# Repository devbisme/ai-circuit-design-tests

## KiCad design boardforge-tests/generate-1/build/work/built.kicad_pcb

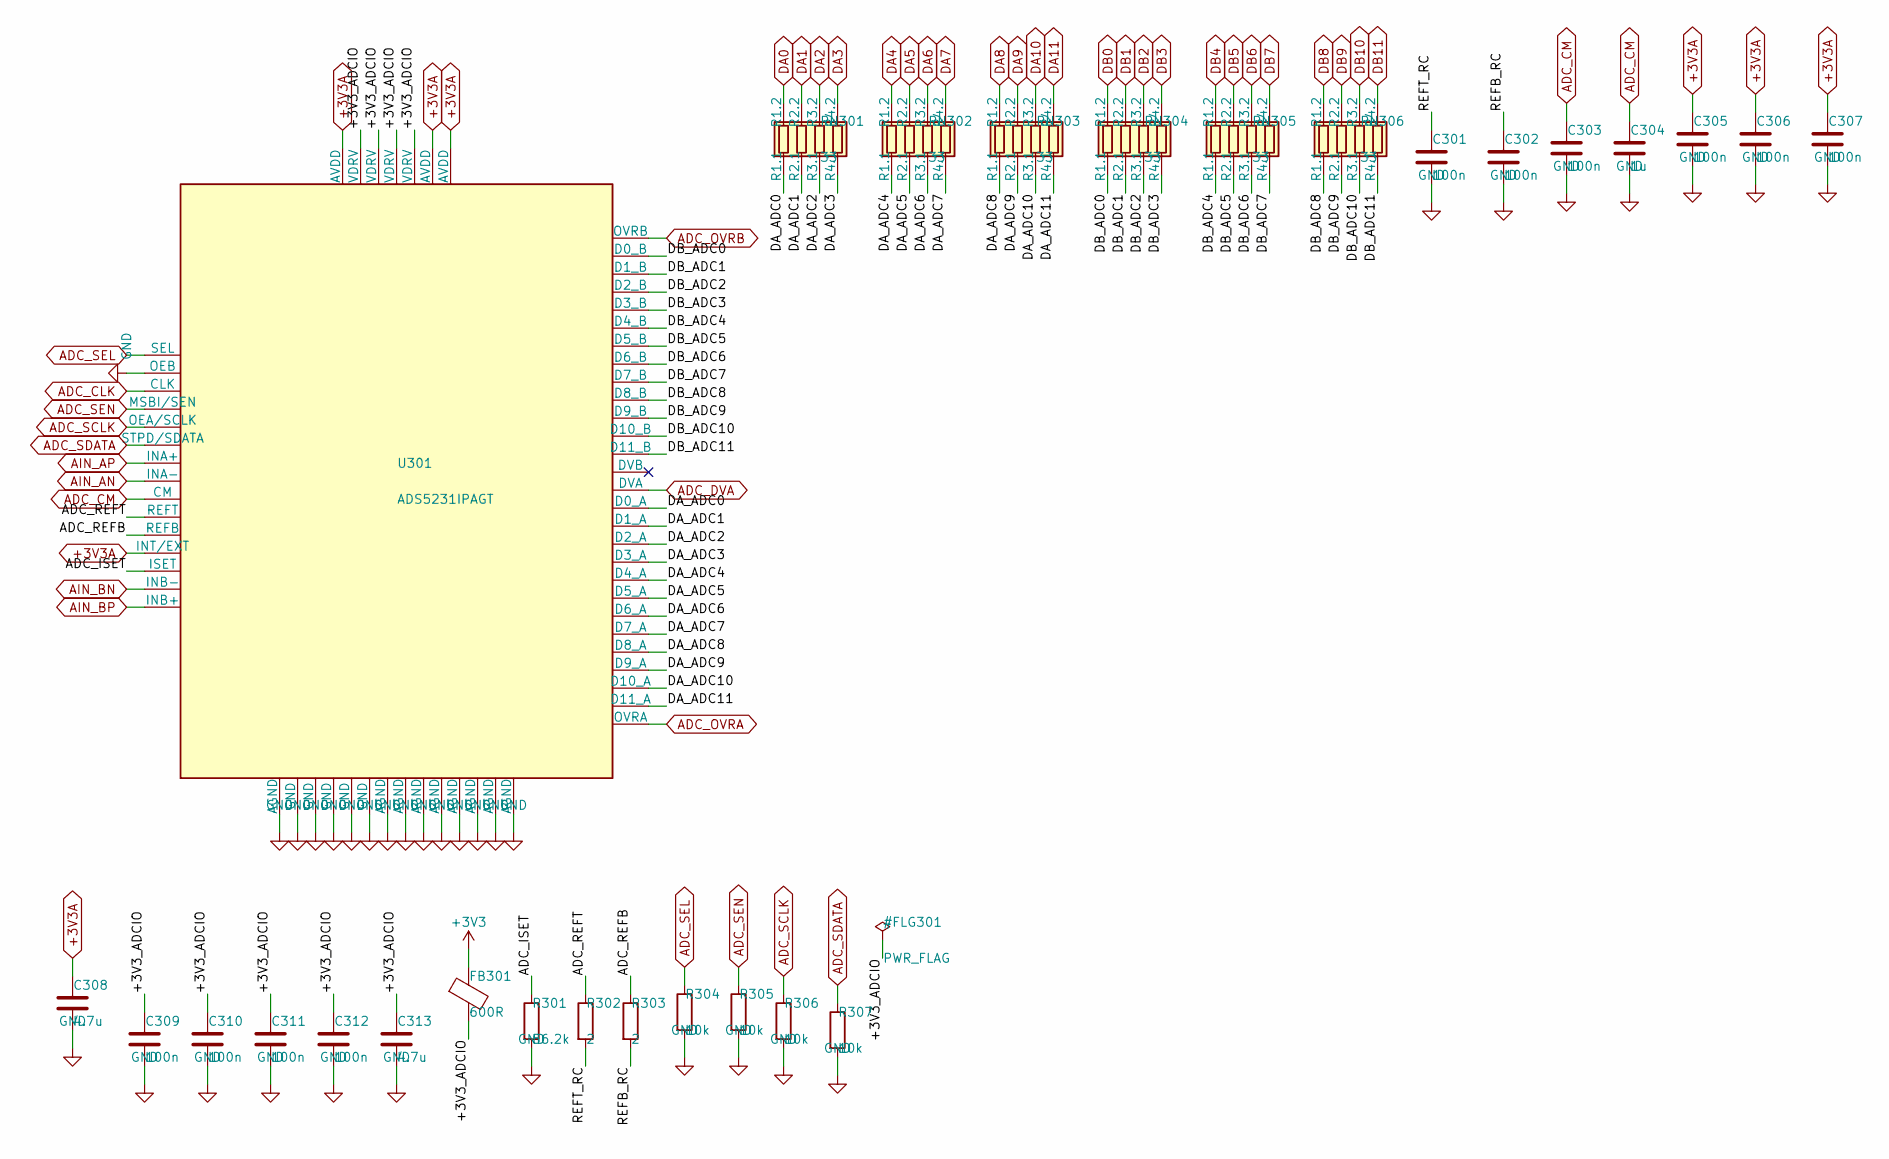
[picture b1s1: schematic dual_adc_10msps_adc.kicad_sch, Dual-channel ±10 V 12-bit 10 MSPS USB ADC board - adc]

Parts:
C301, C302, C303, C305, C306, C307, C309, C310, C311, C312: 100n; C_0402_1005Metric; MPN CL05B104KB54PNC; LCSC C307331
C304: 1u; C_0402_1005Metric; MPN CL05A105KA5NQNC; LCSC C52923
C308, C313: 4.7u; C_0603_1608Metric; MPN CL10A475KO8NNNC; LCSC C19666
FB301: 600R; L_0603_1608Metric; MPN BLM18KG601SN1D; LCSC C85833
R301: 56.2k; R_0402_1005Metric; MPN FRC0402F5622TS; LCSC C5126096
R302, R303: 2; R_0402_1005Metric; MPN FRC0402F2R00TS; LCSC C2998051
R304, R305, R306, R307: 10k; R_0402_1005Metric; MPN 0402WGF1002TCE; LCSC C25744
RN301, RN302, RN303, RN304, RN305, RN306: 33; R_Array_Convex_4x0402; MPN 4D02WGJ0330TCE; LCSC C25501
U301: ADS5231IPAGT; TQFP-64_10x10mm_P0.5mm; MPN ADS5231IPAGT; LCSC C2670079

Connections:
+3V3: FB301.1; also elsewhere on the board
+3V3A: C305.1, C306.1, C307.1, C308.1, U301.3 (AVDD), U301.46 (AVDD), U301.56 (INT/EXT), U301.57 (AVDD); also elsewhere on the board
/adc/+3V3_ADCIO: C309.1, C310.1, C311.1, C312.1, C313.1, FB301.2, U301.5 (VDRV), U301.8 (VDRV), U301.40 (VDRV), U301.43 (VDRV)
/adc/ADC_ISET: R301.1, U301.60 (ISET)
/adc/ADC_REFB: R303.1, U301.54 (REFB)
/adc/ADC_REFT: R302.1, U301.53 (REFT)
/adc/DA_ADC0: RN301.1 (R1.1), U301.27 (D0_A)
/adc/DA_ADC1: RN301.2 (R2.1), U301.28 (D1_A)
/adc/DA_ADC2: RN301.3 (R3.1), U301.29 (D2_A)
/adc/DA_ADC3: RN301.4 (R4.1), U301.30 (D3_A)
/adc/DA_ADC4: RN302.1 (R1.1), U301.31 (D4_A)
/adc/DA_ADC5: RN302.2 (R2.1), U301.32 (D5_A)
/adc/DA_ADC6: RN302.3 (R3.1), U301.33 (D6_A)
/adc/DA_ADC7: RN302.4 (R4.1), U301.34 (D7_A)
/adc/DA_ADC8: RN303.1 (R1.1), U301.35 (D8_A)
/adc/DA_ADC9: RN303.2 (R2.1), U301.36 (D9_A)
/adc/DA_ADC10: RN303.3 (R3.1), U301.37 (D10_A)
/adc/DA_ADC11: RN303.4 (R4.1), U301.38 (D11_A)
/adc/DB_ADC0: RN304.1 (R1.1), U301.10 (D0_B)
/adc/DB_ADC1: RN304.2 (R2.1), U301.11 (D1_B)
/adc/DB_ADC2: RN304.3 (R3.1), U301.12 (D2_B)
/adc/DB_ADC3: RN304.4 (R4.1), U301.13 (D3_B)
/adc/DB_ADC4: RN305.1 (R1.1), U301.14 (D4_B)
/adc/DB_ADC5: RN305.2 (R2.1), U301.15 (D5_B)
/adc/DB_ADC6: RN305.3 (R3.1), U301.16 (D6_B)
/adc/DB_ADC7: RN305.4 (R4.1), U301.17 (D7_B)
/adc/DB_ADC8: RN306.1 (R1.1), U301.18 (D8_B)
/adc/DB_ADC9: RN306.2 (R2.1), U301.19 (D9_B)
/adc/DB_ADC10: RN306.3 (R3.1), U301.20 (D10_B)
/adc/DB_ADC11: RN306.4 (R4.1), U301.21 (D11_B)
/adc/REFB_RC: C302.1, R303.2
/adc/REFT_RC: C301.1, R302.2
ADC_CLK: U301.24 (CLK); also elsewhere on the board
ADC_CM: C303.1, C304.1, U301.52 (CM); also elsewhere on the board
ADC_DVA: U301.26 (DVA); also elsewhere on the board
ADC_OVRA: U301.39 (OVRA); also elsewhere on the board
ADC_OVRB: U301.9 (OVRB); also elsewhere on the board
ADC_SCLK: R306.1, U301.42 (OEA/SCLK); also elsewhere on the board
ADC_SDATA: R307.1, U301.45 (STPD/SDATA); also elsewhere on the board
ADC_SEL: R304.1, U301.1 (SEL); also elsewhere on the board
ADC_SEN: R305.1, U301.41 (MSBI/SEN); also elsewhere on the board
AIN_AN: U301.51 (INA-); also elsewhere on the board
AIN_AP: U301.50 (INA+); also elsewhere on the board
AIN_BN: U301.62 (INB-); also elsewhere on the board
AIN_BP: U301.63 (INB+); also elsewhere on the board
DA0: RN301.8 (R1.2); also elsewhere on the board
DA1: RN301.7 (R2.2); also elsewhere on the board
DA2: RN301.6 (R3.2); also elsewhere on the board
DA3: RN301.5 (R4.2); also elsewhere on the board
DA4: RN302.8 (R1.2); also elsewhere on the board
DA5: RN302.7 (R2.2); also elsewhere on the board
DA6: RN302.6 (R3.2); also elsewhere on the board
DA7: RN302.5 (R4.2); also elsewhere on the board
DA8: RN303.8 (R1.2); also elsewhere on the board
DA9: RN303.7 (R2.2); also elsewhere on the board
DA10: RN303.6 (R3.2); also elsewhere on the board
DA11: RN303.5 (R4.2); also elsewhere on the board
DB0: RN304.8 (R1.2); also elsewhere on the board
DB1: RN304.7 (R2.2); also elsewhere on the board
DB2: RN304.6 (R3.2); also elsewhere on the board
DB3: RN304.5 (R4.2); also elsewhere on the board
DB4: RN305.8 (R1.2); also elsewhere on the board
DB5: RN305.7 (R2.2); also elsewhere on the board
DB6: RN305.6 (R3.2); also elsewhere on the board
DB7: RN305.5 (R4.2); also elsewhere on the board
DB8: RN306.8 (R1.2); also elsewhere on the board
DB9: RN306.7 (R2.2); also elsewhere on the board
DB10: RN306.6 (R3.2); also elsewhere on the board
DB11: RN306.5 (R4.2); also elsewhere on the board
GND: C301.2, C302.2, C303.2, C304.2, C305.2, C306.2, C307.2, C308.2, C309.2, C310.2, C311.2, C312.2, C313.2, R301.2, R304.2, R305.2, R306.2, R307.2, U301.2 (AGND), U301.4 (GND), U301.6 (OEB), U301.7 (GND), U301.23 (GND), U301.25 (GND), U301.44 (GND), U301.47 (AGND), U301.48 (AGND), U301.49 (AGND), U301.55 (AGND), U301.58 (AGND), U301.59 (AGND), U301.61 (AGND), U301.64 (AGND); also elsewhere on the board

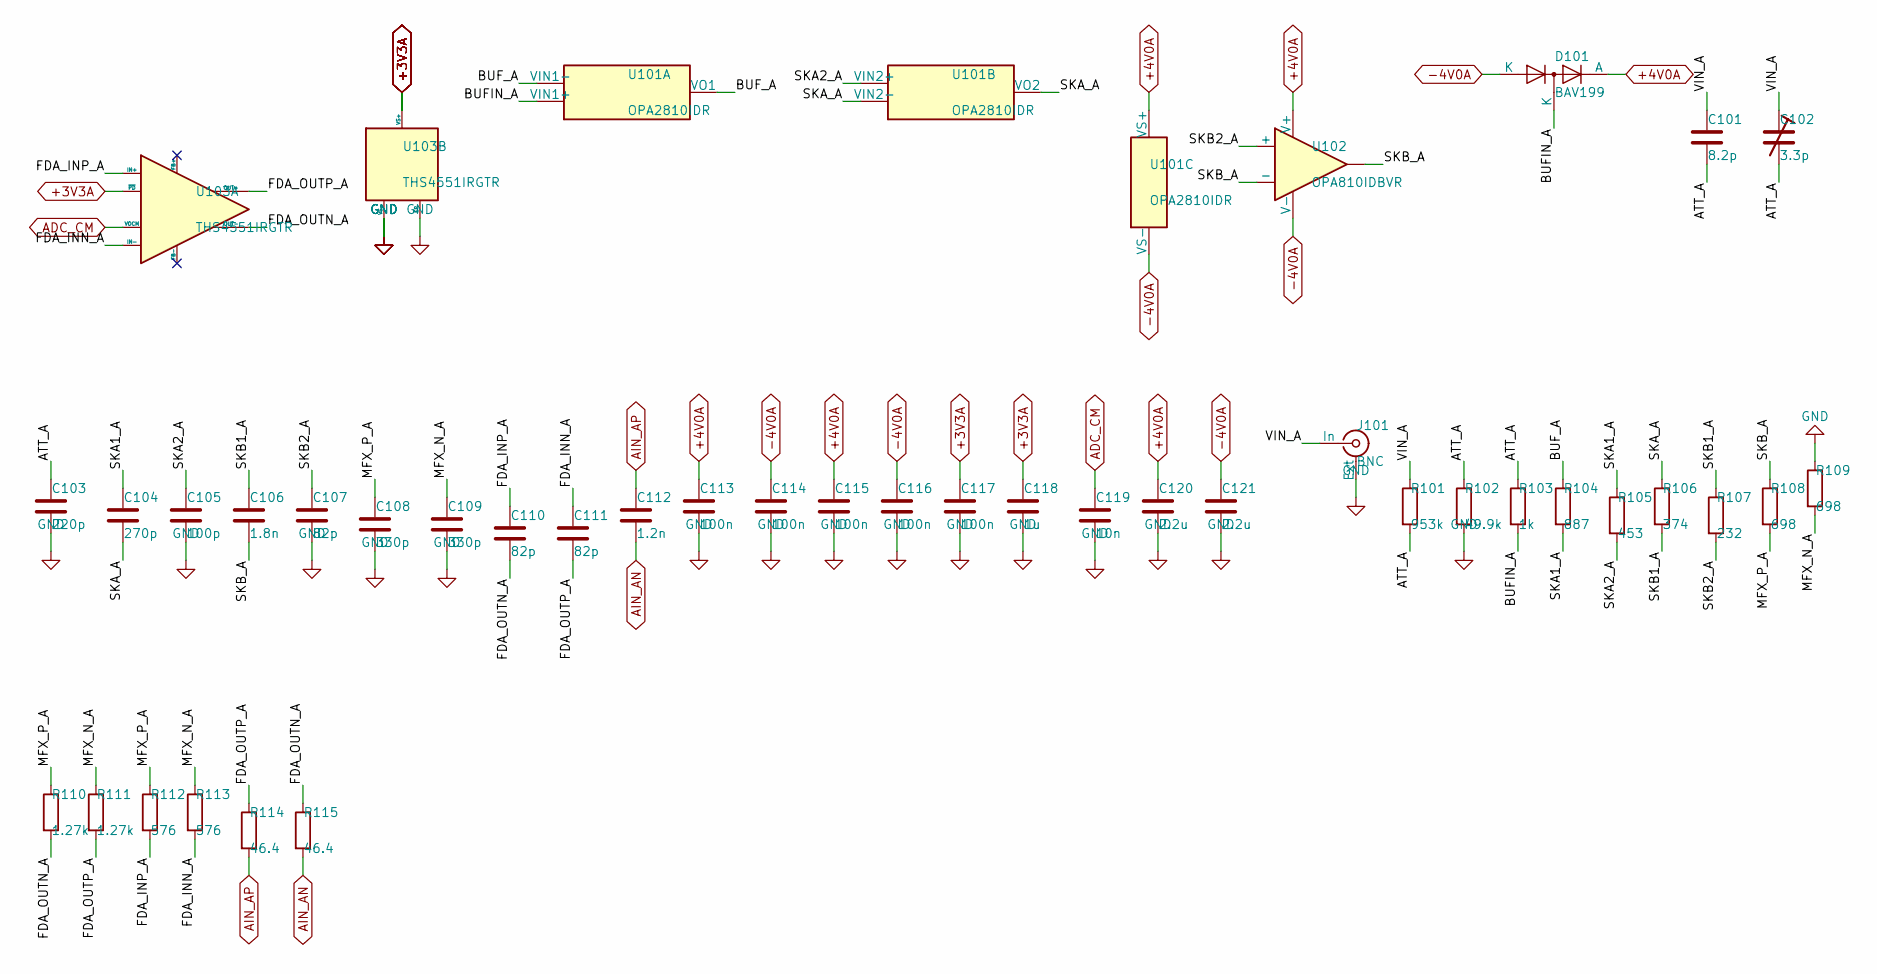
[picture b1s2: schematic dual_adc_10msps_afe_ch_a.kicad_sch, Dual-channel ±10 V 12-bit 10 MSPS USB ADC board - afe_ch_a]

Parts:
C101: 8.2p; C_0603_1608Metric; MPN GQM1875C2E8R2CB12D; LCSC C3874850
C102: 3.3p; C_Trimmer_SEHWA_STC3MA06; MPN STC3MA06-T1; LCSC C22468120
C103: 220p; C_0603_1608Metric; MPN GCM1885C2A221JA16D; LCSC C388907
C104: 270p; C_0402_1005Metric; MPN GRM1555C1H271GA01D; LCSC C161546
C105: 100p; C_0603_1608Metric; MPN 0603CG101G500NT; LCSC C182932
C106: 1.8n; C_0603_1608Metric; MPN GRM1885C1H182FA01D; LCSC C882525
C107, C110, C111: 82p; C_0603_1608Metric; MPN GQM1875C2E820GB12D; LCSC C2171259
C108, C109: 330p; C_0402_1005Metric; MPN GRM1555C1H331GA01D; LCSC C237507
C112: 1.2n; C_0603_1608Metric; MPN GCM1885C1H122FA16D; LCSC C1517816
C113, C114, C115, C116, C117: 100n; C_0402_1005Metric; MPN CL05B104KB54PNC; LCSC C307331
C118: 1u; C_0402_1005Metric; MPN CL05A105KA5NQNC; LCSC C52923
C119: 10n; C_0402_1005Metric; MPN CL05B103KB5NNNC; LCSC C15195
C120, C121: 2.2u; C_0603_1608Metric; MPN CL10A225KO8NNNC; LCSC C23630
D101: BAV199; SOT-23; MPN BAV199; LCSC C68971
J101: BNC; BNC_KH-BNC50-3511; MPN KH-BNC50-3511; LCSC C2837587
R101: 953k; R_1206_3216Metric; MPN WR12X9533FTL; LCSC C368327
R102: 49.9k; R_0603_1608Metric; MPN 0603WAF4992T5E; LCSC C23184
R103: 1k; R_0603_1608Metric; MPN 0603WAF1001T5E; LCSC C21190
R104: 887; R_0402_1005Metric; MPN CRCW0402887RFKED; LCSC C4012675
R105: 453; R_0402_1005Metric; MPN FRC0402F4530TS; LCSC C5126227
R106: 374; R_0402_1005Metric; MPN RMS04FT3740; LCSC C208875
R107: 232; R_0402_1005Metric; MPN GR0402F232RTAG00; LCSC C49655645
R108, R109: 698; R_0402_1005Metric; MPN GR0402F698RTAG00; LCSC C49655034
R110, R111: 1.27k; R_0402_1005Metric; MPN FRC0402F1271TS; LCSC C3013151
R112, R113: 576; R_0402_1005Metric; MPN 0402WGF5760TCE; LCSC C45320
R114, R115: 46.4; R_0402_1005Metric; MPN RC0402FR-0746R4L; LCSC C273734
U101: OPA2810IDR; SOIC-8_3.9x4.9mm_P1.27mm; MPN OPA2810IDR; LCSC C1849413
U102: OPA810IDBVR; SOT-23-5; MPN OPA810IDBVR; LCSC C2833513
U103: THS4551IRGTR; VQFN-16-1EP_3x3mm_P0.5mm_EP1.68x1.68mm; MPN THS4551IRGTR; LCSC C2869590

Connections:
+3V3A: C117.1, C118.1, U103.5 (VS+), U103.6 (VS+), U103.7 (VS+), U103.8 (VS+), U103.12 (~PD); also elsewhere on the board
+4V0A: C113.1, C115.1, C120.1, D101.2 (A), U101.8 (VS+), U102.5 (V+); also elsewhere on the board
-4V0A: C114.1, C116.1, C121.1, D101.1 (K), U101.4 (VS-), U102.2 (V-); also elsewhere on the board
/afe_ch_a/ATT_A: C101.2, C102.2, C103.1, R101.2, R102.1, R103.1
/afe_ch_a/BUFIN_A: D101.3 (K), R103.2, U101.3 (VIN1+)
/afe_ch_a/BUF_A: R104.1, U101.1 (VO1), U101.2 (VIN1-)
/afe_ch_a/FDA_INN_A: C111.1, R113.2, U103.3 (IN-)
/afe_ch_a/FDA_INP_A: C110.1, R112.2, U103.2 (IN+)
/afe_ch_a/FDA_OUTN_A: C110.2, R110.2, R115.1, U103.11 (OUT-)
/afe_ch_a/FDA_OUTP_A: C111.2, R111.2, R114.1, U103.10 (OUT+)
/afe_ch_a/MFX_N_A: C109.1, R109.2, R111.1, R113.1
/afe_ch_a/MFX_P_A: C108.1, R108.2, R110.1, R112.1
/afe_ch_a/SKA1_A: C104.1, R104.2, R105.1
/afe_ch_a/SKA2_A: C105.1, R105.2, U101.5 (VIN2+)
/afe_ch_a/SKA_A: C104.2, R106.1, U101.6 (VIN2-), U101.7 (VO2)
/afe_ch_a/SKB1_A: C106.1, R106.2, R107.1
/afe_ch_a/SKB2_A: C107.1, R107.2, U102.3 (+)
/afe_ch_a/SKB_A: C106.2, R108.1, U102.1, U102.4 (-)
/afe_ch_a/VIN_A: C101.1, C102.1, J101.1 (In), R101.1
ADC_CM: C119.1, U103.9 (VOCM); also elsewhere on the board
AIN_AN: C112.2, R115.2; also elsewhere on the board
AIN_AP: C112.1, R114.2; also elsewhere on the board
GND: C103.2, C105.2, C107.2, C108.2, C109.2, C113.2, C114.2, C115.2, C116.2, C117.2, C118.2, C119.2, C120.2, C121.2, J101.2 (Ext), R102.2, R109.1, U103.13 (VS-), U103.14 (VS-), U103.15 (VS-), U103.16 (VS-), U103.17 (EP); also elsewhere on the board

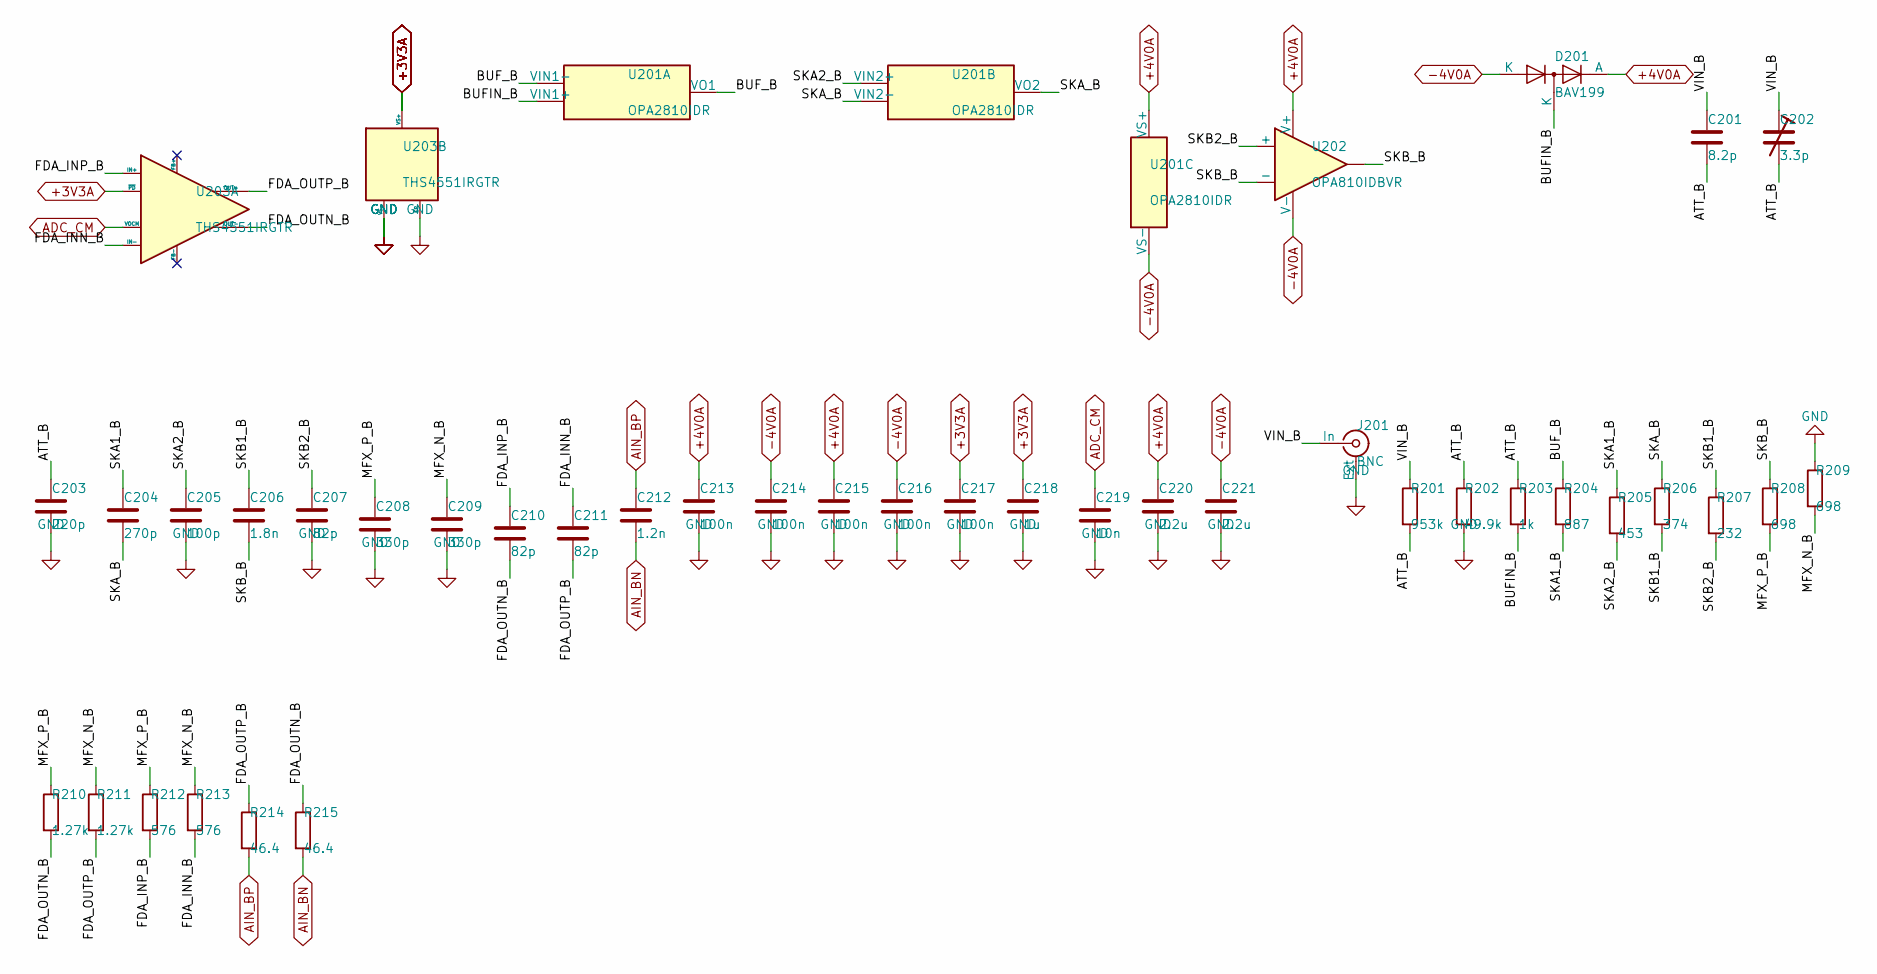
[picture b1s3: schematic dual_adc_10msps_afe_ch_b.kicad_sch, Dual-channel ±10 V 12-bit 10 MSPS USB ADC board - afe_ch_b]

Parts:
C201: 8.2p; C_0603_1608Metric; MPN GQM1875C2E8R2CB12D; LCSC C3874850
C202: 3.3p; C_Trimmer_SEHWA_STC3MA06; MPN STC3MA06-T1; LCSC C22468120
C203: 220p; C_0603_1608Metric; MPN GCM1885C2A221JA16D; LCSC C388907
C204: 270p; C_0402_1005Metric; MPN GRM1555C1H271GA01D; LCSC C161546
C205: 100p; C_0603_1608Metric; MPN 0603CG101G500NT; LCSC C182932
C206: 1.8n; C_0603_1608Metric; MPN GRM1885C1H182FA01D; LCSC C882525
C207, C210, C211: 82p; C_0603_1608Metric; MPN GQM1875C2E820GB12D; LCSC C2171259
C208, C209: 330p; C_0402_1005Metric; MPN GRM1555C1H331GA01D; LCSC C237507
C212: 1.2n; C_0603_1608Metric; MPN GCM1885C1H122FA16D; LCSC C1517816
C213, C214, C215, C216, C217: 100n; C_0402_1005Metric; MPN CL05B104KB54PNC; LCSC C307331
C218: 1u; C_0402_1005Metric; MPN CL05A105KA5NQNC; LCSC C52923
C219: 10n; C_0402_1005Metric; MPN CL05B103KB5NNNC; LCSC C15195
C220, C221: 2.2u; C_0603_1608Metric; MPN CL10A225KO8NNNC; LCSC C23630
D201: BAV199; SOT-23; MPN BAV199; LCSC C68971
J201: BNC; BNC_KH-BNC50-3511; MPN KH-BNC50-3511; LCSC C2837587
R201: 953k; R_1206_3216Metric; MPN WR12X9533FTL; LCSC C368327
R202: 49.9k; R_0603_1608Metric; MPN 0603WAF4992T5E; LCSC C23184
R203: 1k; R_0603_1608Metric; MPN 0603WAF1001T5E; LCSC C21190
R204: 887; R_0402_1005Metric; MPN CRCW0402887RFKED; LCSC C4012675
R205: 453; R_0402_1005Metric; MPN FRC0402F4530TS; LCSC C5126227
R206: 374; R_0402_1005Metric; MPN RMS04FT3740; LCSC C208875
R207: 232; R_0402_1005Metric; MPN GR0402F232RTAG00; LCSC C49655645
R208, R209: 698; R_0402_1005Metric; MPN GR0402F698RTAG00; LCSC C49655034
R210, R211: 1.27k; R_0402_1005Metric; MPN FRC0402F1271TS; LCSC C3013151
R212, R213: 576; R_0402_1005Metric; MPN 0402WGF5760TCE; LCSC C45320
R214, R215: 46.4; R_0402_1005Metric; MPN RC0402FR-0746R4L; LCSC C273734
U201: OPA2810IDR; SOIC-8_3.9x4.9mm_P1.27mm; MPN OPA2810IDR; LCSC C1849413
U202: OPA810IDBVR; SOT-23-5; MPN OPA810IDBVR; LCSC C2833513
U203: THS4551IRGTR; VQFN-16-1EP_3x3mm_P0.5mm_EP1.68x1.68mm; MPN THS4551IRGTR; LCSC C2869590

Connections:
+3V3A: C217.1, C218.1, U203.5 (VS+), U203.6 (VS+), U203.7 (VS+), U203.8 (VS+), U203.12 (~PD); also elsewhere on the board
+4V0A: C213.1, C215.1, C220.1, D201.2 (A), U201.8 (VS+), U202.5 (V+); also elsewhere on the board
-4V0A: C214.1, C216.1, C221.1, D201.1 (K), U201.4 (VS-), U202.2 (V-); also elsewhere on the board
/afe_ch_b/ATT_B: C201.2, C202.2, C203.1, R201.2, R202.1, R203.1
/afe_ch_b/BUFIN_B: D201.3 (K), R203.2, U201.3 (VIN1+)
/afe_ch_b/BUF_B: R204.1, U201.1 (VO1), U201.2 (VIN1-)
/afe_ch_b/FDA_INN_B: C211.1, R213.2, U203.3 (IN-)
/afe_ch_b/FDA_INP_B: C210.1, R212.2, U203.2 (IN+)
/afe_ch_b/FDA_OUTN_B: C210.2, R210.2, R215.1, U203.11 (OUT-)
/afe_ch_b/FDA_OUTP_B: C211.2, R211.2, R214.1, U203.10 (OUT+)
/afe_ch_b/MFX_N_B: C209.1, R209.2, R211.1, R213.1
/afe_ch_b/MFX_P_B: C208.1, R208.2, R210.1, R212.1
/afe_ch_b/SKA1_B: C204.1, R204.2, R205.1
/afe_ch_b/SKA2_B: C205.1, R205.2, U201.5 (VIN2+)
/afe_ch_b/SKA_B: C204.2, R206.1, U201.6 (VIN2-), U201.7 (VO2)
/afe_ch_b/SKB1_B: C206.1, R206.2, R207.1
/afe_ch_b/SKB2_B: C207.1, R207.2, U202.3 (+)
/afe_ch_b/SKB_B: C206.2, R208.1, U202.1, U202.4 (-)
/afe_ch_b/VIN_B: C201.1, C202.1, J201.1 (In), R201.1
ADC_CM: C219.1, U203.9 (VOCM); also elsewhere on the board
AIN_BN: C212.2, R215.2; also elsewhere on the board
AIN_BP: C212.1, R214.2; also elsewhere on the board
GND: C203.2, C205.2, C207.2, C208.2, C209.2, C213.2, C214.2, C215.2, C216.2, C217.2, C218.2, C219.2, C220.2, C221.2, J201.2 (Ext), R202.2, R209.1, U203.13 (VS-), U203.14 (VS-), U203.15 (VS-), U203.16 (VS-), U203.17 (EP); also elsewhere on the board

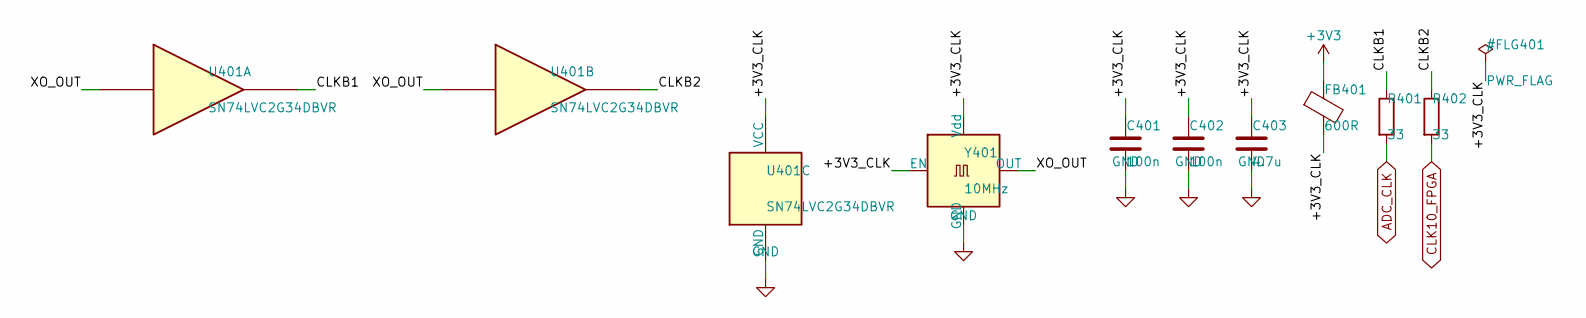
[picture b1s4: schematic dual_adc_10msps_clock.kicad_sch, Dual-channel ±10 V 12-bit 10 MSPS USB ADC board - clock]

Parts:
C401, C402: 100n; C_0402_1005Metric; MPN CL05B104KB54PNC; LCSC C307331
C403: 4.7u; C_0603_1608Metric; MPN CL10A475KO8NNNC; LCSC C19666
FB401: 600R; L_0603_1608Metric; MPN BLM18KG601SN1D; LCSC C85833
R401, R402: 33; R_0402_1005Metric; MPN 0402WGF330JTCE; LCSC C25105
U401: SN74LVC2G34DBVR; SOT-23-6; MPN SN74LVC2G34DBVR; LCSC C7394039
Y401: 10MHz; Oscillator_SMD_Abracon_ASE-4Pin_3.2x2.5mm; MPN SX3M10.000B10F20TNN; LCSC C5452682

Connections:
+3V3: FB401.1; also elsewhere on the board
/clock/+3V3_CLK: C401.1, C402.1, C403.1, FB401.2, U401.5 (VCC), Y401.1 (EN), Y401.4 (Vdd)
/clock/CLKB1: R401.1, U401.6
/clock/CLKB2: R402.1, U401.4
/clock/XO_OUT: U401.1, U401.3, Y401.3 (OUT)
ADC_CLK: R401.2; also elsewhere on the board
CLK10_FPGA: R402.2; also elsewhere on the board
GND: C401.2, C402.2, C403.2, U401.2 (GND), Y401.2 (GND); also elsewhere on the board

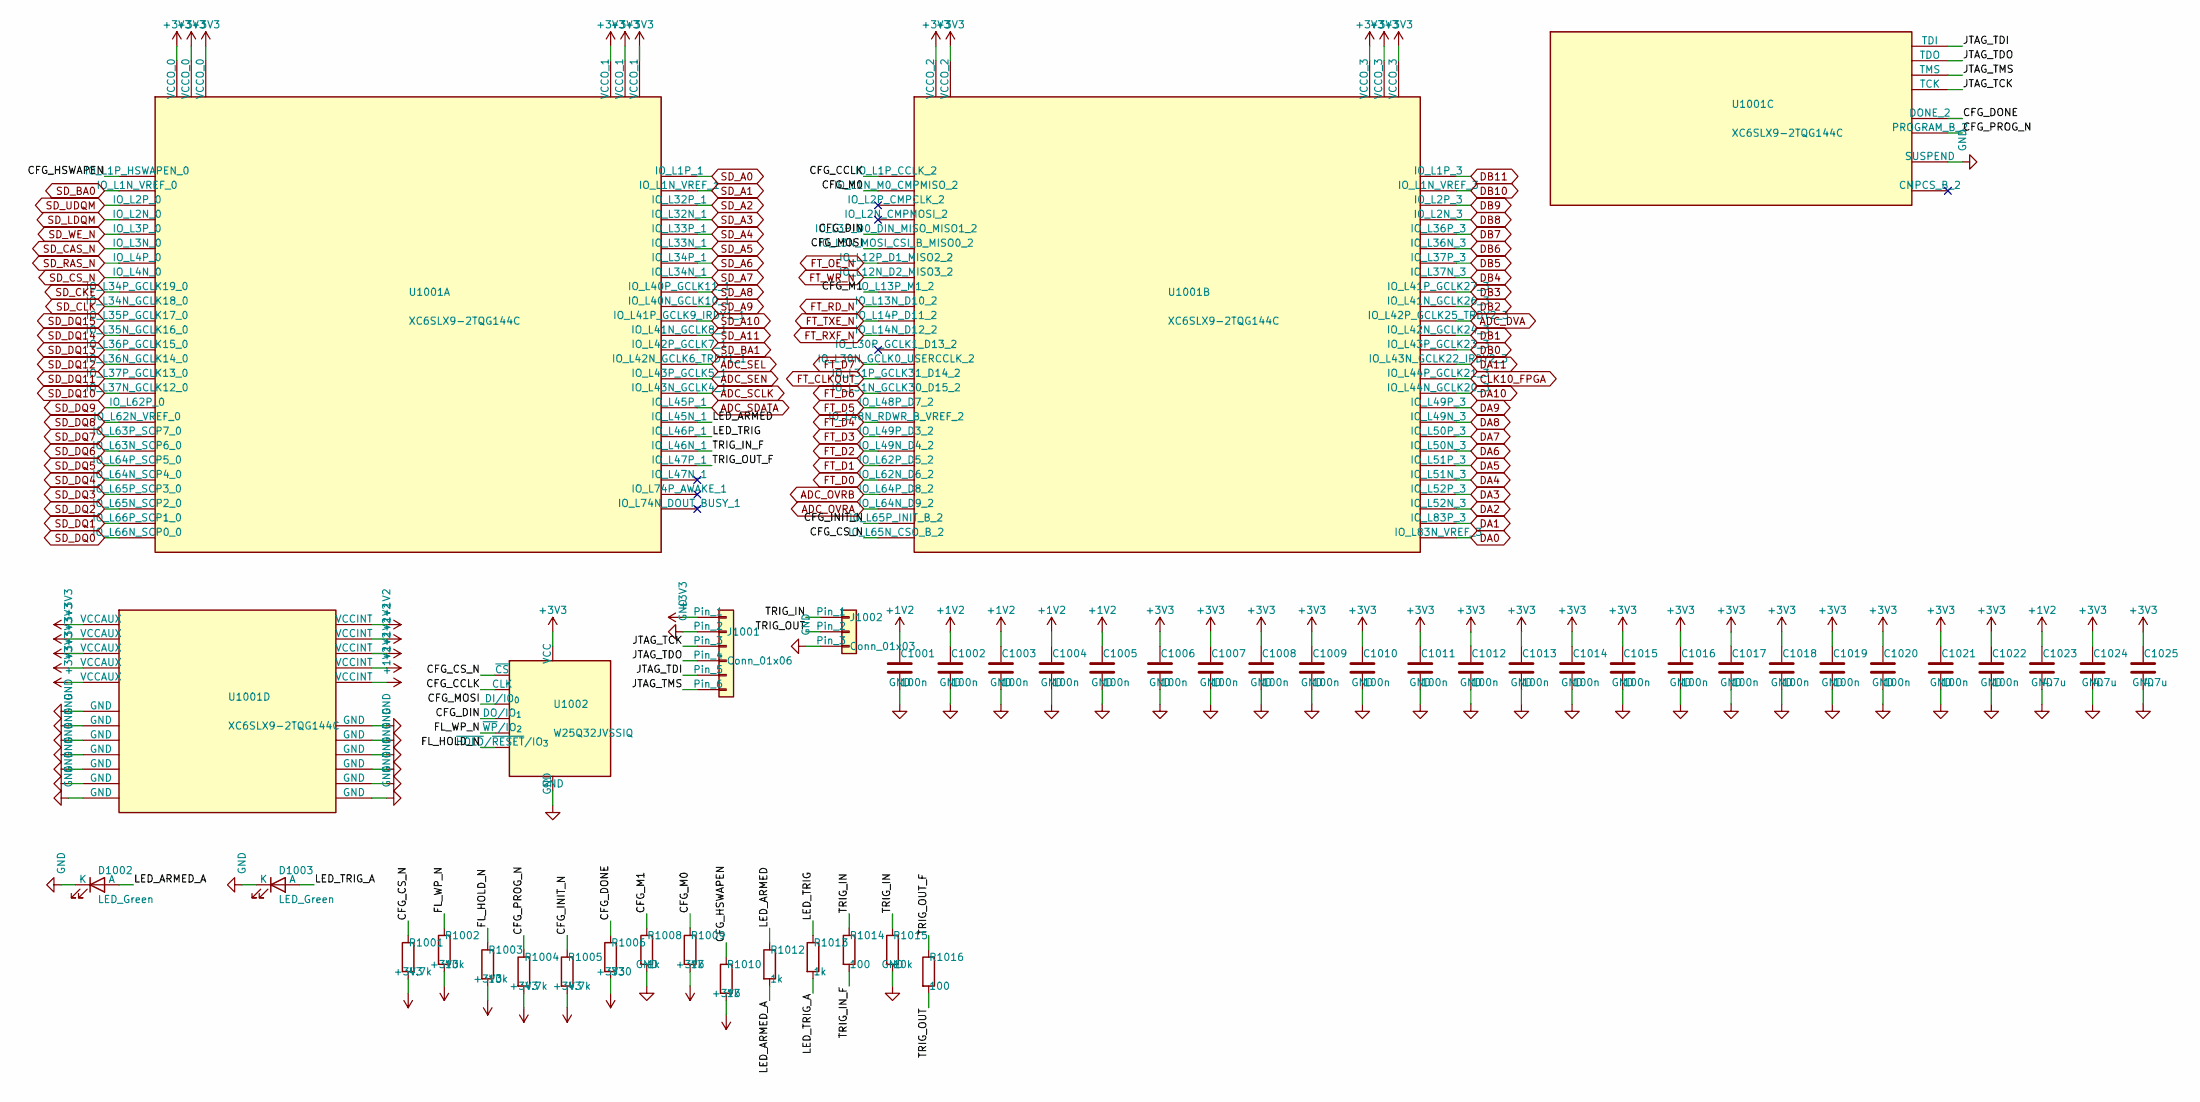
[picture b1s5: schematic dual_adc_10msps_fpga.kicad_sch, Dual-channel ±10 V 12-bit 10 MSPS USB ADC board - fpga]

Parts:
C1001, C1002, C1003, C1004, C1005, C1006, C1007, C1008, C1009, C1010, C1011, C1012, C1013, C1014, C1015, C1016, C1017, C1018, C1019, C1020, C1021, C1022: 100n; C_0402_1005Metric; MPN CL05B104KB54PNC; LCSC C307331
C1023, C1024, C1025: 4.7u; C_0603_1608Metric; MPN CL10A475KO8NNNC; LCSC C19666
D1002, D1003: LED_Green; LED_0603_1608Metric; MPN PSC-1608U52GC-G4; LCSC C22371297
J1001: Conn_01x06; PinHeader_1x06_P2.54mm_Vertical; MPN PZ254V-11-06P; LCSC C492405
J1002: Conn_01x03; PinHeader_1x03_P2.54mm_Vertical; MPN PZ254V-11-03P; LCSC C2937625
R1001, R1004, R1005: 4.7k; R_0402_1005Metric; MPN 0402WGF4701TCE; LCSC C25900
R1002, R1003, R1015: 10k; R_0402_1005Metric; MPN 0402WGF1002TCE; LCSC C25744
R1006: 330; R_0402_1005Metric; MPN 0402WGF3300TCE; LCSC C25104
R1008, R1009, R1010, R1012, R1013: 1k; R_0402_1005Metric; MPN 0402WGF1001TCE; LCSC C11702
R1014, R1016: 100; R_0402_1005Metric; MPN 0402WGF1000TCE; LCSC C25076
U1001: XC6SLX9-2TQG144C; TQFP-144_20x20mm_P0.5mm; MPN XC6SLX9-2TQG144C; LCSC C27408
U1002: W25Q32JVSSIQ; SOIC-8_5.3x5.3mm_P1.27mm; MPN W25Q32JVSSIQ; LCSC C179173

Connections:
+1V2: C1001.1, C1002.1, C1003.1, C1004.1, C1005.1, C1023.1, U1001.19 (VCCINT), U1001.28 (VCCINT), U1001.52 (VCCINT), U1001.89 (VCCINT), U1001.128 (VCCINT); also elsewhere on the board
+3V3: C1006.1, C1007.1, C1008.1, C1009.1, C1010.1, C1011.1, C1012.1, C1013.1, C1014.1, C1015.1, C1016.1, C1017.1, C1018.1, C1019.1, C1020.1, C1021.1, C1022.1, C1024.1, C1025.1, J1001.1, R1001.2, R1002.2, R1003.2, R1004.2, R1005.2, R1006.2, R1009.2, R1010.2, U1001.4 (VCCO_3), U1001.18 (VCCO_3), U1001.20 (VCCAUX), U1001.31 (VCCO_3), U1001.36 (VCCAUX), U1001.42 (VCCO_2), U1001.53 (VCCAUX), U1001.63 (VCCO_2), U1001.76 (VCCO_1), U1001.86 (VCCO_1), U1001.90 (VCCAUX), U1001.103 (VCCO_1), U1001.122 (VCCO_0), U1001.125 (VCCO_0), U1001.129 (VCCAUX), U1001.135 (VCCO_0), U1002.8 (VCC); also elsewhere on the board
/fpga/CFG_CCLK: U1001.70 (IO_L1P_CCLK_2), U1002.6 (CLK)
/fpga/CFG_CS_N: R1001.1, U1001.38 (IO_L65N_CSO_B_2), U1002.1 (~CS)
/fpga/CFG_DIN: U1001.65 (IO_L3P_D0_DIN_MISO_MISO1_2), U1002.2 (DO/IO_{1})
/fpga/CFG_DONE: R1006.1, U1001.71 (DONE_2)
/fpga/CFG_HSWAPEN: R1010.1, U1001.144 (IO_L1P_HSWAPEN_0)
/fpga/CFG_INIT_N: R1005.1, U1001.39 (IO_L65P_INIT_B_2)
/fpga/CFG_M0: R1009.1, U1001.69 (IO_L1N_M0_CMPMISO_2)
/fpga/CFG_M1: R1008.1, U1001.60 (IO_L13P_M1_2)
/fpga/CFG_MOSI: U1001.64 (IO_L3N_MOSI_CSI_B_MISO0_2), U1002.5 (DI/IO_{0})
/fpga/CFG_PROG_N: R1004.1, U1001.37 (PROGRAM_B_2)
/fpga/FL_HOLD_N: R1003.1, U1002.7 (~HOLD/~RESET/IO_{3})
/fpga/FL_WP_N: R1002.1, U1002.3 (~WP/IO_{2})
/fpga/JTAG_TCK: J1001.3, U1001.109 (TCK)
/fpga/JTAG_TDI: J1001.5, U1001.110 (TDI)
/fpga/JTAG_TDO: J1001.4, U1001.106 (TDO)
/fpga/JTAG_TMS: J1001.6, U1001.107 (TMS)
/fpga/LED_ARMED: R1012.1, U1001.82 (IO_L45N_1)
/fpga/LED_ARMED_A: D1002.2 (A), R1012.2
/fpga/LED_TRIG: R1013.1, U1001.81 (IO_L46P_1)
/fpga/LED_TRIG_A: D1003.2 (A), R1013.2
/fpga/TRIG_IN: J1002.1, R1014.1, R1015.1
/fpga/TRIG_IN_F: R1014.2, U1001.80 (IO_L46N_1)
/fpga/TRIG_OUT: J1002.2, R1016.2
/fpga/TRIG_OUT_F: R1016.1, U1001.79 (IO_L47P_1)
ADC_DVA: U1001.22 (IO_L42P_GCLK25_TRDY2_3); also elsewhere on the board
ADC_OVRA: U1001.40 (IO_L64N_D9_2); also elsewhere on the board
ADC_OVRB: U1001.41 (IO_L64P_D8_2); also elsewhere on the board
ADC_SCLK: U1001.84 (IO_L43N_GCLK4_1); also elsewhere on the board
ADC_SDATA: U1001.83 (IO_L45P_1); also elsewhere on the board
ADC_SEL: U1001.87 (IO_L42N_GCLK6_TRDY1_1); also elsewhere on the board
ADC_SEN: U1001.85 (IO_L43P_GCLK5_1); also elsewhere on the board
CLK10_FPGA: U1001.15 (IO_L44P_GCLK21_3); also elsewhere on the board
DA0: U1001.1 (IO_L83N_VREF_3); also elsewhere on the board
DA1: U1001.2 (IO_L83P_3); also elsewhere on the board
DA2: U1001.5 (IO_L52N_3); also elsewhere on the board
DA3: U1001.6 (IO_L52P_3); also elsewhere on the board
DA4: U1001.7 (IO_L51N_3); also elsewhere on the board
DA5: U1001.8 (IO_L51P_3); also elsewhere on the board
DA6: U1001.9 (IO_L50N_3); also elsewhere on the board
DA7: U1001.10 (IO_L50P_3); also elsewhere on the board
DA8: U1001.11 (IO_L49N_3); also elsewhere on the board
DA9: U1001.12 (IO_L49P_3); also elsewhere on the board
DA10: U1001.14 (IO_L44N_GCLK20_3); also elsewhere on the board
DA11: U1001.16 (IO_L43N_GCLK22_IRDY2_3); also elsewhere on the board
DB0: U1001.17 (IO_L43P_GCLK23_3); also elsewhere on the board
DB1: U1001.21 (IO_L42N_GCLK24_3); also elsewhere on the board
DB2: U1001.23 (IO_L41N_GCLK26_3); also elsewhere on the board
DB3: U1001.24 (IO_L41P_GCLK27_3); also elsewhere on the board
DB4: U1001.26 (IO_L37N_3); also elsewhere on the board
DB5: U1001.27 (IO_L37P_3); also elsewhere on the board
DB6: U1001.29 (IO_L36N_3); also elsewhere on the board
DB7: U1001.30 (IO_L36P_3); also elsewhere on the board
DB8: U1001.32 (IO_L2N_3); also elsewhere on the board
DB9: U1001.33 (IO_L2P_3); also elsewhere on the board
DB10: U1001.34 (IO_L1N_VREF_3); also elsewhere on the board
DB11: U1001.35 (IO_L1P_3); also elsewhere on the board
FT_CLKOUT: U1001.51 (IO_L31P_GCLK31_D14_2); also elsewhere on the board
FT_D0: U1001.43 (IO_L62N_D6_2); also elsewhere on the board
FT_D1: U1001.44 (IO_L62P_D5_2); also elsewhere on the board
FT_D2: U1001.45 (IO_L49N_D4_2); also elsewhere on the board
FT_D3: U1001.46 (IO_L49P_D3_2); also elsewhere on the board
FT_D4: U1001.47 (IO_L48N_RDWR_B_VREF_2); also elsewhere on the board
FT_D5: U1001.48 (IO_L48P_D7_2); also elsewhere on the board
FT_D6: U1001.50 (IO_L31N_GCLK30_D15_2); also elsewhere on the board
FT_D7: U1001.55 (IO_L30N_GCLK0_USERCCLK_2); also elsewhere on the board
FT_OE_N: U1001.62 (IO_L12P_D1_MISO2_2); also elsewhere on the board
FT_RD_N: U1001.59 (IO_L13N_D10_2); also elsewhere on the board
FT_RXF_N: U1001.57 (IO_L14N_D12_2); also elsewhere on the board
FT_TXE_N: U1001.58 (IO_L14P_D11_2); also elsewhere on the board
FT_WR_N: U1001.61 (IO_L12N_D2_MISO3_2); also elsewhere on the board
GND: C1001.2, C1002.2, C1003.2, C1004.2, C1005.2, C1006.2, C1007.2, C1008.2, C1009.2, C1010.2, C1011.2, C1012.2, C1013.2, C1014.2, C1015.2, C1016.2, C1017.2, C1018.2, C1019.2, C1020.2, C1021.2, C1022.2, C1023.2, C1024.2, C1025.2, D1002.1 (K), D1003.1 (K), J1001.2, J1002.3, R1008.2, R1015.2, U1001.3 (GND), U1001.13 (GND), U1001.25 (GND), U1001.49 (GND), U1001.54 (GND), U1001.68 (GND), U1001.73 (SUSPEND), U1001.77 (GND), U1001.91 (GND), U1001.96 (GND), U1001.108 (GND), U1001.113 (GND), U1001.130 (GND), U1001.136 (GND), U1002.4 (GND); also elsewhere on the board
SD_A0: U1001.105 (IO_L1P_1); also elsewhere on the board
SD_A1: U1001.104 (IO_L1N_VREF_1); also elsewhere on the board
SD_A2: U1001.102 (IO_L32P_1); also elsewhere on the board
SD_A3: U1001.101 (IO_L32N_1); also elsewhere on the board
SD_A4: U1001.100 (IO_L33P_1); also elsewhere on the board
SD_A5: U1001.99 (IO_L33N_1); also elsewhere on the board
SD_A6: U1001.98 (IO_L34P_1); also elsewhere on the board
SD_A7: U1001.97 (IO_L34N_1); also elsewhere on the board
SD_A8: U1001.95 (IO_L40P_GCLK11_1); also elsewhere on the board
SD_A9: U1001.94 (IO_L40N_GCLK10_1); also elsewhere on the board
SD_A10: U1001.93 (IO_L41P_GCLK9_IRDY1_1); also elsewhere on the board
SD_A11: U1001.92 (IO_L41N_GCLK8_1); also elsewhere on the board
SD_BA0: U1001.143 (IO_L1N_VREF_0); also elsewhere on the board
SD_BA1: U1001.88 (IO_L42P_GCLK7_1); also elsewhere on the board
SD_CAS_N: U1001.139 (IO_L3N_0); also elsewhere on the board
SD_CKE: U1001.134 (IO_L34P_GCLK19_0); also elsewhere on the board
SD_CLK: U1001.133 (IO_L34N_GCLK18_0); also elsewhere on the board
SD_CS_N: U1001.137 (IO_L4N_0); also elsewhere on the board
SD_DQ0: U1001.111 (IO_L66N_SCP0_0); also elsewhere on the board
SD_DQ1: U1001.112 (IO_L66P_SCP1_0); also elsewhere on the board
SD_DQ2: U1001.114 (IO_L65N_SCP2_0); also elsewhere on the board
SD_DQ3: U1001.115 (IO_L65P_SCP3_0); also elsewhere on the board
SD_DQ4: U1001.116 (IO_L64N_SCP4_0); also elsewhere on the board
SD_DQ5: U1001.117 (IO_L64P_SCP5_0); also elsewhere on the board
SD_DQ6: U1001.118 (IO_L63N_SCP6_0); also elsewhere on the board
SD_DQ7: U1001.119 (IO_L63P_SCP7_0); also elsewhere on the board
SD_DQ8: U1001.120 (IO_L62N_VREF_0); also elsewhere on the board
SD_DQ9: U1001.121 (IO_L62P_0); also elsewhere on the board
SD_DQ10: U1001.123 (IO_L37N_GCLK12_0); also elsewhere on the board
SD_DQ11: U1001.124 (IO_L37P_GCLK13_0); also elsewhere on the board
SD_DQ12: U1001.126 (IO_L36N_GCLK14_0); also elsewhere on the board
SD_DQ13: U1001.127 (IO_L36P_GCLK15_0); also elsewhere on the board
SD_DQ14: U1001.131 (IO_L35N_GCLK16_0); also elsewhere on the board
SD_DQ15: U1001.132 (IO_L35P_GCLK17_0); also elsewhere on the board
SD_LDQM: U1001.141 (IO_L2N_0); also elsewhere on the board
SD_RAS_N: U1001.138 (IO_L4P_0); also elsewhere on the board
SD_UDQM: U1001.142 (IO_L2P_0); also elsewhere on the board
SD_WE_N: U1001.140 (IO_L3P_0); also elsewhere on the board
